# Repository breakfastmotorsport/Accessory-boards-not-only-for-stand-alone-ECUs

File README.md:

# Accessory boards not only for stand-alone ECUs

Fairly universal utility PCBs to help with the smaller stuff.

* [AFR indicator light](AFR-indicator-light)
* [555 On-Delay](555-on-delay)
* [TO-220 FET Mount](TO-220-FET-mount)
* [Cable Management for WTMtronics UA4C and NO2C Speeduino boards](cable_management_for_UA4C_NO2C)
* [FFC Adapter 16-pin](ffc-adapter-16pin)

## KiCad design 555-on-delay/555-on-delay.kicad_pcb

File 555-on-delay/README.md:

# 555 On-Delay

Delays the power-on of a device. A TO-220 FET is used to switch device GND. Useful e.g. for wide-band O2 controllers.

Traces for source and drain are duplicated on the back layer of the PCB. Wires up to 1.5 mm² (16 AWG) can be soldered to the board. LED negative differs a bit from the schematic.

Dimension: 60 x 20 mm

Mounting hole pattern: 45 x 15 mm (3.5 mm hole diameter)

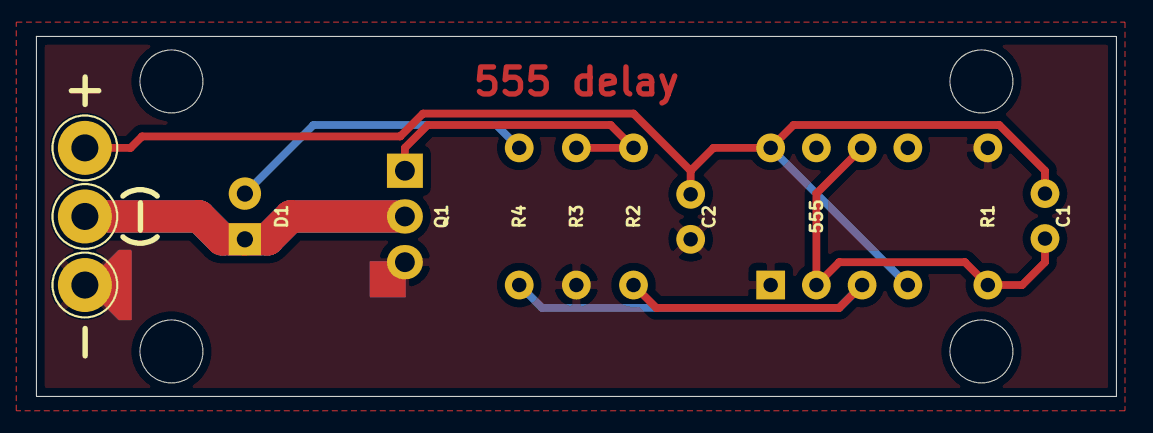
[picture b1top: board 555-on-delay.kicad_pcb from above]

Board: 2 copper layers, 60.0 x 20.0 mm, 12 parts (0 on the bottom side), 7 nets.

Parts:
555: NE555; DIP-8_W7.62mm
+: MountingHole_Pad; Pin_D1.3mm_L11.0mm_LooseFit
-: MountingHole_Pad; Pin_D1.3mm_L11.0mm_LooseFit
-#2: MountingHole_Pad; Pin_D1.3mm_L11.0mm_LooseFit
C1: 100u; C_Disc_D5.0mm_W2.5mm_P2.50mm
C2: 0.1u; C_Disc_D5.0mm_W2.5mm_P2.50mm
D1: LED; LED_D5.0mm
Q1: some TO-220 FET; TO-220-3_Vertical
R1: 10M; R_Axial_DIN0207_L6.3mm_D2.5mm_P7.62mm_Horizontal
R2: 1k; R_Axial_DIN0207_L6.3mm_D2.5mm_P7.62mm_Horizontal
R3: 100k; R_Axial_DIN0207_L6.3mm_D2.5mm_P7.62mm_Horizontal
R4: 2.4k; R_Axial_DIN0207_L6.3mm_D2.5mm_P7.62mm_Horizontal

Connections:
+12V: 555.4, 555.8, +.1, C1.1, C2.2
GND: 555.1, -#2.1, C2.1, Q1.3, R1.2, R3.2
unnamed: 555.2, 555.6, C1.2, R1.1
unnamed: -.1, D1.1, Q1.2
unnamed: D1.2, R4.2
unnamed: Q1.1, R2.2, R3.1
unnamed: 555.3, R2.1, R4.1

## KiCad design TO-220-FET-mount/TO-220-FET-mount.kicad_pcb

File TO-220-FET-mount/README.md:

# TO-220 FET Mount

The TO-220 FET can be mounted horizontally.

Traces for source and drain are duplicated on the back layer of the PCB. Wires up to 1.5 mm² (16 AWG) can be soldered to the board.

Dimension: 60 x 20 mm

Mounting hole pattern: 45 x 15 mm (3.5 mm hole diameter)

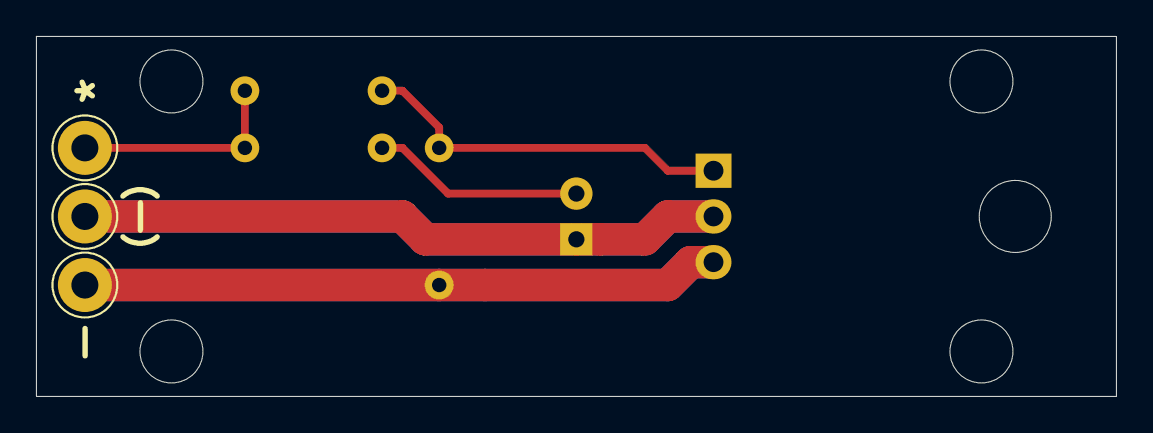
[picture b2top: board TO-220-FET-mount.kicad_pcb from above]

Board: 2 copper layers, 60.0 x 20.0 mm, 8 parts (0 on the bottom side), 5 nets.

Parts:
*: MountingHole_Pad; Pin_D1.3mm_L11.0mm_LooseFit
-: MountingHole_Pad; Pin_D1.3mm_L11.0mm_LooseFit
-#2: MountingHole_Pad; Pin_D1.3mm_L11.0mm_LooseFit
D1: LED; LED_D5.0mm
Q1: IRF3205; TO-220-3_Vertical
R1: 1k; R_Axial_DIN0207_L6.3mm_D2.5mm_P7.62mm_Horizontal
R2: 100k; R_Axial_DIN0207_L6.3mm_D2.5mm_P7.62mm_Horizontal
R3: 2.4k; R_Axial_DIN0207_L6.3mm_D2.5mm_P7.62mm_Horizontal

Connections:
unnamed: -.1, D1.1, Q1.2
unnamed: D1.2, R3.1
unnamed: *.1, R1.2, R3.2
unnamed: Q1.1, R1.1, R2.1
unnamed: -#2.1, Q1.3, R2.2

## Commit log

2021-05-05 Add AFR-indicator-light
2021-05-05 Add Arduino Sketch
